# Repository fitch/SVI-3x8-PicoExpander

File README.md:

# SVI-3x8 PicoExpander

## Overview

The SVI-3x8 PicoExpander is a Raspberry Pico 2 W based expansion device for Spectravideo 318 and 328 computers.

The device emulates (when plugged into the SVI-3x8 expansion port):
 - **96 kB of additional RAM (BK22, BK31, BK32) to SVI-328**, to be used for example with BASIC SWITCH command or CP/M
 - **144 kB more RAM to SVI-318**, converting it to a SVI-328 and allowing games designed for SVI-328 to be run on a 318
 - **Disk emulation (.dsk)** so you can load and save disk images via Wi-Fi
 - **Cassette drive emulation (.cas)** with auto-running, allowing you to finally send and run .CAS images via Wi-Fi
 - **Support for 64 kB ROM game cartridges**, without using the game cartridge slot and finally fixing the 64 kB ROM support in SVI-328 MKII devices
 - **Save states** to save computer state and load it at later time, making it possible to save your progress in a game and continue later
 - **Remote launch** allowing you to pick up a game image from PC/Mac and launch it from the SVI via Wi-Fi
 - **Hard disk emulation** with server-based network backing, allowing CP/M hard disk images to be served over Wi-Fi

## Limitations

Limitations of the current software (1.4.4):
 - Supports only one disk drive, two-disk drive support coming up

## The project

This repository will later include the full software and the hardware design later as open source. Now you can access the 1.4 PCB version in [pcb](pcb/) directory.

If you can't build one yourself, you can order an assembled version from [here](https://svi-328-dev.company.site/products/svi-3x8-picoexpander-1-4). Current shipping estimate in 1-4 weeks depending on the order volumes.

<b>Important note:</b>

This is ”bleeding edge” hardware, so it might not last 40 years as the SVI did. The Pico pins are used with level shifters and within the limits of the voltage thresholds, but the actual Pico CPU is running overclocked at 300 MHz (normally 150 MHz). This might cause the Pico to wear out sooner than Raspberry has designed it to. However, the Pico can be replaced on the board if needed.

Also, note that device is a prototype and therefore has very limited warranty: you can test it when it arrives and if you're not satisfied, we'll figure out if we ship a new one or you get your money back or something else. But everything else is at your own risk. If the device stops working after 3-12 months, you'll need to fix it yourself or get a new one.

## Quick Start

### 1. Flash the Firmware

When you've built the PCB you can flash the .UF2 file provided in the [release](release/) directory. For the assembled devices, the Pico has already been flashed with the latest firmware.

1. Disconnect PicoExpander from SVI
2. Hold the **BOOTSEL** button on the Pico W while connecting it to your computer via USB
3. The Pico will appear as a USB mass storage device
4. Copy the `.uf2` firmware file from the `release/` directory to the Pico USB drive. Wait until Pico disconnects (displays Disk Not Ejected Properly in macOS) and the green LED light turns on to signal that the firmware booted correctly.
5. Finally, remove the USB cable.

### 2. Install Node.js

The file server requires Node.js to run. This project includes an `.nvmrc` file specifying Node.js v22.20.0.

**macOS (using nvm):**

Install [nvm](https://github.com/nvm-sh/nvm) if you don't have it, then:
```bash
# Install and use the correct Node.js version
nvm install
nvm use
```

**Windows:**
Download and install from [nodejs.org](https://nodejs.org/)

### 3. Boot the SVI with PicoExpander

Place the PicoExpander into the expansion port of the SVI-318 or SVI-328. Boot SVI up.

You can return to the main menu in two ways:
- Press the **RESET button** on the PicoExpander briefly
- Press **CTRL + SHIFT + LEFT GRAPH + RIGHT GRAPH** simultaneously on the keyboard

If you need to reset the SVI, press the RESET button for at least 3 seconds.

### 4. Run the File Server

Start the server with a directory containing your disk images, ROMs, and cassette files:

```bash
node js/server.js ./images
```

The server will:
- Scan the directory for supported files (.rom, .dsk, .cas, .sta)
- Connect to the PicoExpander over Wi-Fi
- Serve files to the SVI-328 on demand

Press **H** in the server to see available commands.

## Documentation

For detailed documentation, see the `doc/` directory:

| Document | Description |
|----------|-------------|
| [server.md](doc/server.md) | File server usage and interactive commands |
| [send_command.md](doc/send_command.md) | Command-line tool for scripting and automation |
| [hard-disk-emulation.md](doc/hard-disk-emulation.md) | Hard disk emulation setup and usage |
| [boot-sequence.md](doc/boot-sequence.md) | Technical details of the PicoExpander boot process |
| [io-ports.md](doc/io-ports.md) | I/O port reference for developers |
| [save-state-format.md](doc/save-state-format.md) | Save state file format specification |
| [development.md](doc/development.md) | Building the ROM and development setup |
| [pcb/README.md](pcb/README.md) | PCB design files, schematics overview, and parts list |

## Release Notes

See the latest changes in [v1.4.4 release notes](release/release-notes-1.4.4.md).

## License

Detailed licensing information is documented within the included [LICENSE](LICENSE) file.

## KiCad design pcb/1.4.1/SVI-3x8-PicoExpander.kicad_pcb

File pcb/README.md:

# SVI-3x8 PicoExpander PCB

## Overview

This directory contains the KiCad hardware design files for the SVI-3x8 PicoExpander and the SuperExpander adapter board.

## Projects

### PicoExpander (main board)

The main expansion board that connects to the SVI-3x8 expansion port via a 50-pin edge connector.

- **KiCad project:** [SVI-3x8-PicoExpander.kicad_pro](SVI-3x8-PicoExpander.kicad_pro)
- **Schematic:** [SVI-3x8-PicoExpander.kicad_sch](SVI-3x8-PicoExpander.kicad_sch)
- **PCB layout:** [SVI-3x8-PicoExpander.kicad_pcb](SVI-3x8-PicoExpander.kicad_pcb)
- **Schematics PDF:** [schematics.pdf](../photos/schematics.pdf)

### SuperExpander Adapter

A simple passive adapter board that allows the PicoExpander to be connected to the Spectravideo SuperExpander (SVI-605) instead of directly to the computer's expansion port.

- **KiCad project:** [SVI-3x8-PicoExpander-SuperExpander-adapter.kicad_pro](SVI-3x8-PicoExpander-SuperExpander-adapter.kicad_pro)
- **PCB layout:** [SVI-3x8-PicoExpander-SuperExpander-adapter.kicad_pcb](SVI-3x8-PicoExpander-SuperExpander-adapter.kicad_pcb)

### Gerber Files

Manufacturing-ready Gerber files are available in the [gerber/](gerber/) directory:

- [gerber/PicoExpander/](gerber/PicoExpander/) — Main board Gerbers
- [gerber/SuperExpander adapter/](gerber/SuperExpander%20adapter/) — Adapter board Gerbers

## Schematics Overview

The PicoExpander circuit consists of:

- **Raspberry Pi Pico 2 W (A1)** — The main microcontroller running the emulation firmware at 300 MHz. Connects to the SVI bus through level shifters and handles all emulation logic, Wi-Fi connectivity, and flash storage.

- **4x 74LVC245A level shifters (U1, U2, U4, U5)** — Bidirectional bus transceivers that translate between the SVI's 5V bus and the Pico's 3.3V logic levels:
  - **U5** — Data bus write (SVI → Pico, active during bus writes)
  - **U1** — Data bus read (Pico → SVI, active during bus reads)
  - **U2** — Lower address bus A0–A7
  - **U4** — Higher address bus A8–A15

- **74HC14 Schmitt trigger (U3, 7 gates used)** — Provides clean signal conditioning for active-low control signals from the SVI bus: `/RST`, `/ROMDIS`, `/RD`, `/WR`, `/MREQ`, `/P_AE` (address enable), and `/P_RD_DE`/`/P_WR_DE` (data direction enable).

- **50-pin edge connector (J1)** — Interfaces directly with the SVI-3x8 expansion bus, providing access to the full address bus, data bus, and control signals.

- **Reset button (SW1)** — Short press returns to the PicoExpander menu. Long press (3+ seconds) resets the SVI.

- **Pull-up resistor (R1, 10kΩ)** — Pull-up on the reset line.

- **Decoupling capacitors (C2–C5, 0.1μF)** — One per level shifter IC for power supply filtering.

## Parts List

| Ref | Qty | Description | DigiKey Part | DigiKey # |
|-----|-----|-------------|-------------|-----------|
| A1 | 1 | Raspberry Pi Pico 2 W (RP2350) | [SC1634](https://www.digikey.com/en/products/detail/raspberry-pi/SC1634/26241087) | 2648-SC1634-ND |
| U1, U2, U4, U5 | 4 | 74LVC245A — Bidirectional level shifter, 3.6V, 20-PDIP | [SN74LVC245AN](https://www.digikey.com/en/products/detail/texas-instruments/SN74LVC245AN/377483) | 296-8503-5-ND |
| U3 | 1 | 74HC14 — Hex Schmitt trigger inverter, 14-DIP | [SN74AHCT14N](https://www.digikey.com/en/products/detail/texas-instruments/SN74AHCT14N/375854) | 296-4674-5-ND |
| C2–C5 | 4 | 0.1μF ceramic capacitor, 50V, X7R, radial | [K104K15X7RF5TL2](https://www.digikey.com/en/products/detail/vishay-beyschlag-draloric-bc-components/K104K15X7RF5TL2/286538) | BC1084CT-ND |
| R1 | 1 | 10kΩ resistor, 1/4W, 1%, axial | [MFR-25FRF52-10K](https://www.digikey.com/en/products/detail/yageo/MFR-25FRF52-10K/14626) | 13-MFR-25FRF52-10KCT-ND |
| J1 | 1 | 50-pin (2x25) card edge connector, dual female, 0.100" pitch | [395-050-524-202](https://www.digikey.com/en/products/detail/edac-inc/395-050-524-202/1297302) | 395-050-524-202-ND |
| SW1 | 1 | Tactile push button switch, SPST-NO, 0.05A, 12V | [PTS636 SP43 LFS](https://www.digikey.com/product-detail/en/c-k/PTS636-SP43-LFS/CKN12304-ND/10071717) | CKN12304-ND |

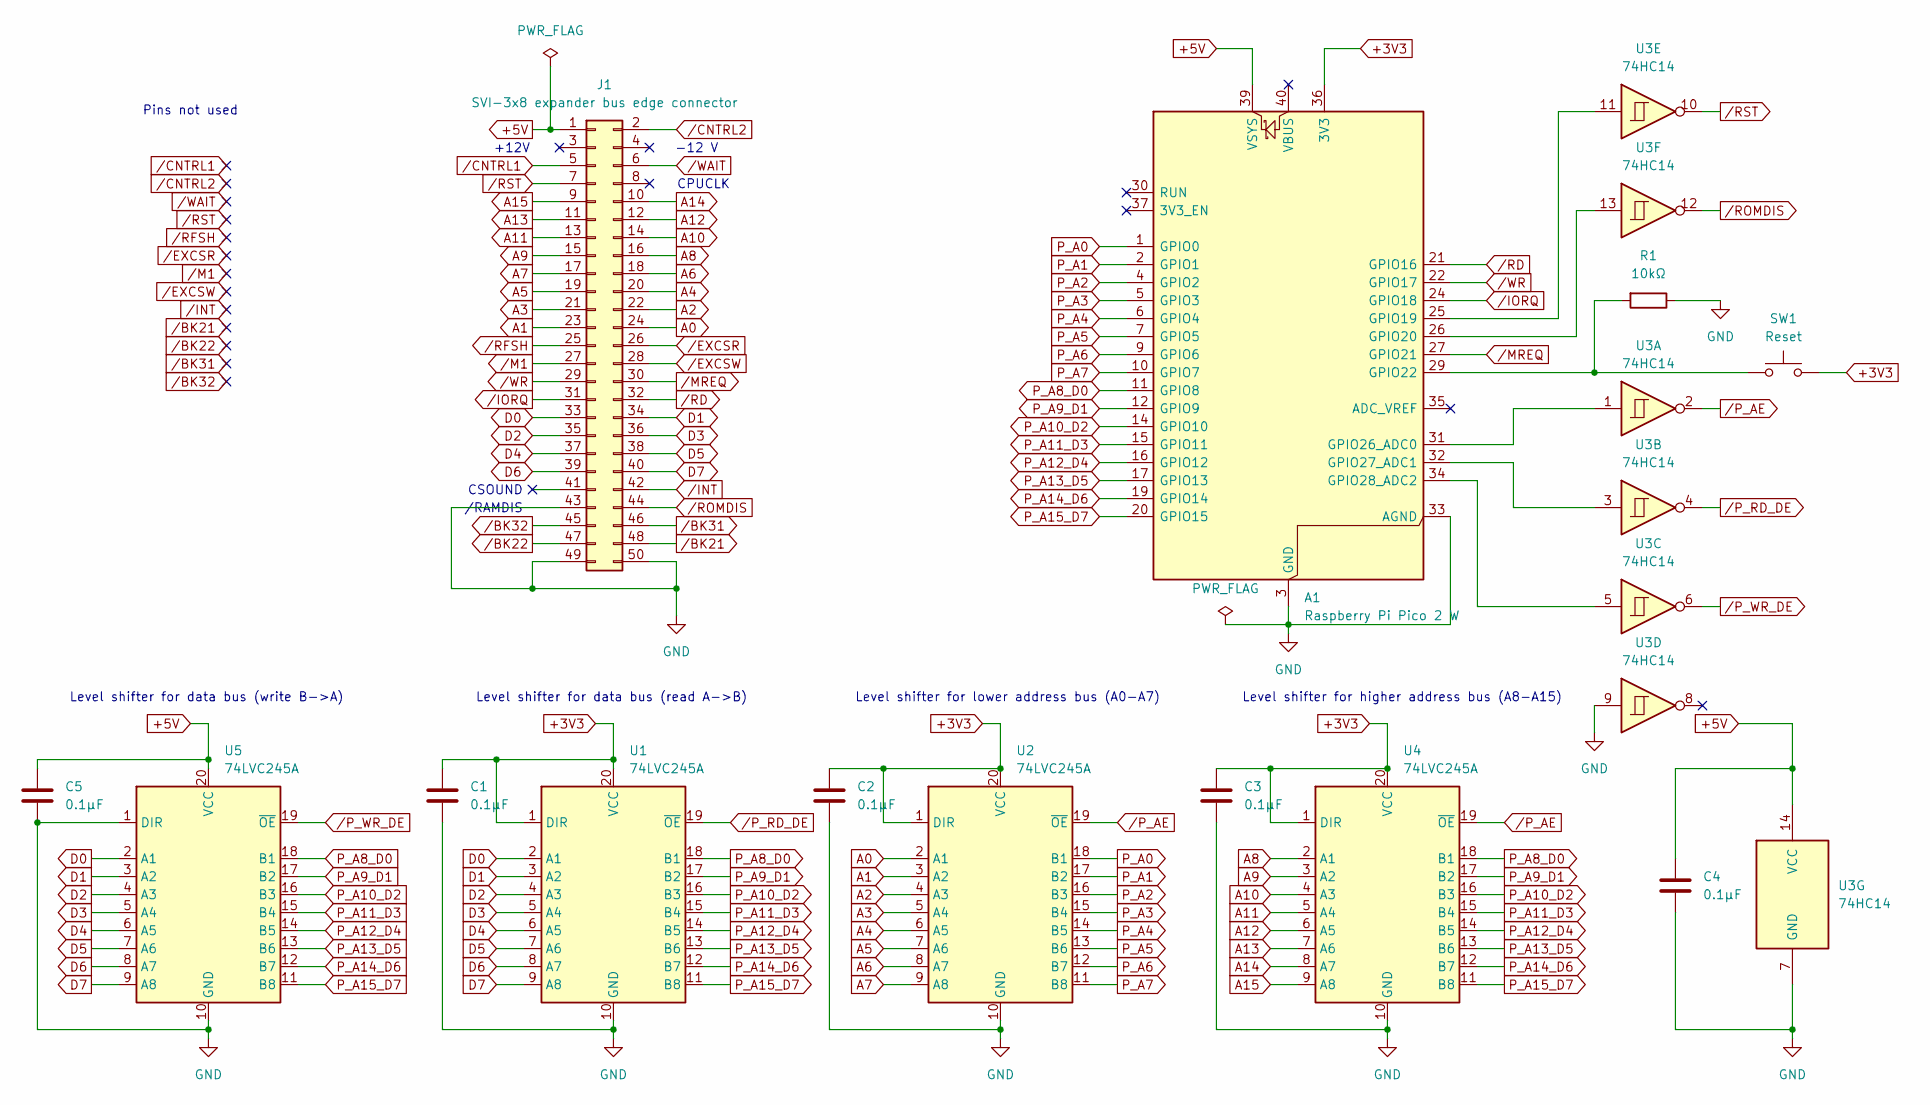
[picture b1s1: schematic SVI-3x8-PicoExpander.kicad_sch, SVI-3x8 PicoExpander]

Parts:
A1: Raspberry Pi Pico 2 W; RaspberryPi_Pico_Common_Unspecified
C1, C2, C3, C4, C5: 0.1μF; C_Disc_D3.0mm_W1.6mm_P2.50mm
J1: SVI-3x8 expander bus edge connector; DIP-50_EXPANDER_BUS
R1: 10kΩ; R_Axial_DIN0207_L6.3mm_D2.5mm_P7.62mm_Horizontal
SW1: Reset; SW_PUSH_1P1T_6x3.5mm_H4.3_APEM_MJTP1243
U1, U2, U4, U5: 74LVC245A; DIP-20_W7.62mm
U3: 74HC14; DIP-14_W7.62mm

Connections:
+3V3: A1.36 (3V3), C1.1, C2.1, C3.1, SW1.2, U1.1 (DIR), U1.20 (VCC), U2.1 (DIR), U2.20 (VCC), U4.1 (DIR), U4.20 (VCC)
+5V: A1.39 (VSYS), C4.1, C5.1, J1.1, U3.14 (VCC), U5.20 (VCC)
A0: J1.24, U2.2 (A1)
A1: J1.23, U2.3 (A2)
A2: J1.22, U2.4 (A3)
A3: J1.21, U2.5 (A4)
A4: J1.20, U2.6 (A5)
A5: J1.19, U2.7 (A6)
A6: J1.18, U2.8 (A7)
A7: J1.17, U2.9 (A8)
A8: J1.16, U4.2 (A1)
A9: J1.15, U4.3 (A2)
A10: J1.14, U4.4 (A3)
A11: J1.13, U4.5 (A4)
A12: J1.12, U4.6 (A5)
A13: J1.11, U4.7 (A6)
A14: J1.10, U4.8 (A7)
A15: J1.9, U4.9 (A8)
D0: J1.33, U1.2 (A1), U5.2 (A1)
D1: J1.34, U1.3 (A2), U5.3 (A2)
D2: J1.35, U1.4 (A3), U5.4 (A3)
D3: J1.36, U1.5 (A4), U5.5 (A4)
D4: J1.37, U1.6 (A5), U5.6 (A5)
D5: J1.38, U1.7 (A6), U5.7 (A6)
D6: J1.39, U1.8 (A7), U5.8 (A7)
D7: J1.40, U1.9 (A8), U5.9 (A8)
GND: A1.3 (GND), A1.8 (GND), A1.13 (GND), A1.18 (GND), A1.23 (GND), A1.28 (GND), A1.33 (AGND), A1.38 (GND), C1.2, C2.2, C3.2, C4.2, C5.2, J1.43, J1.49, J1.50, R1.1, U1.10 (GND), U2.10 (GND), U3.7 (GND), U3.9, U4.10 (GND), U5.1 (DIR), U5.10 (GND)
unnamed: A1.25 (GPIO19), U3.11
unnamed: A1.26 (GPIO20), U3.13
unnamed: A1.29 (GPIO22), R1.2, SW1.1
unnamed: A1.31 (GPIO26_ADC0), U3.1
unnamed: A1.32 (GPIO27_ADC1), U3.3
unnamed: A1.34 (GPIO28_ADC2), U3.5
P_A0: A1.1 (GPIO0), U2.18 (B1)
P_A1: A1.2 (GPIO1), U2.17 (B2)
P_A2: A1.4 (GPIO2), U2.16 (B3)
P_A3: A1.5 (GPIO3), U2.15 (B4)
P_A4: A1.6 (GPIO4), U2.14 (B5)
P_A5: A1.7 (GPIO5), U2.13 (B6)
P_A6: A1.9 (GPIO6), U2.12 (B7)
P_A7: A1.10 (GPIO7), U2.11 (B8)
P_A8_D0: A1.11 (GPIO8), U1.18 (B1), U4.18 (B1), U5.18 (B1)
P_A9_D1: A1.12 (GPIO9), U1.17 (B2), U4.17 (B2), U5.17 (B2)
P_A10_D2: A1.14 (GPIO10), U1.16 (B3), U4.16 (B3), U5.16 (B3)
P_A11_D3: A1.15 (GPIO11), U1.15 (B4), U4.15 (B4), U5.15 (B4)
P_A12_D4: A1.16 (GPIO12), U1.14 (B5), U4.14 (B5), U5.14 (B5)
P_A13_D5: A1.17 (GPIO13), U1.13 (B6), U4.13 (B6), U5.13 (B6)
P_A14_D6: A1.19 (GPIO14), U1.12 (B7), U4.12 (B7), U5.12 (B7)
P_A15_D7: A1.20 (GPIO15), U1.11 (B8), U4.11 (B8), U5.11 (B8)
/BK21: J1.48
/BK22: J1.47
/BK31: J1.46
/BK32: J1.45
/CNTRL1: J1.5
/CNTRL2: J1.2
/EXCSR: J1.26
/EXCSW: J1.28
/INT: J1.42
/IORQ: A1.24 (GPIO18), J1.31
/M1: J1.27
/MREQ: A1.27 (GPIO21), J1.30
/P_AE: U2.19 (~OE), U3.2, U4.19 (~OE)
/P_RD_DE: U1.19 (~OE), U3.4
/P_WR_DE: U3.6, U5.19 (~OE)
/RD: A1.21 (GPIO16), J1.32
/RFSH: J1.25
/ROMDIS: J1.44, U3.12
/RST: J1.7, U3.10
/WAIT: J1.6
/WR: A1.22 (GPIO17), J1.29

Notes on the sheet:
-12 V
+12V
Level shifter for data bus (read A->B)
CSOUND
Level shifter for data bus (write B->A)
Level shifter for higher address bus (A8-A15)
Level shifter for lower address bus (A0-A7)
CPUCLK
/RAMDIS
Pins not used

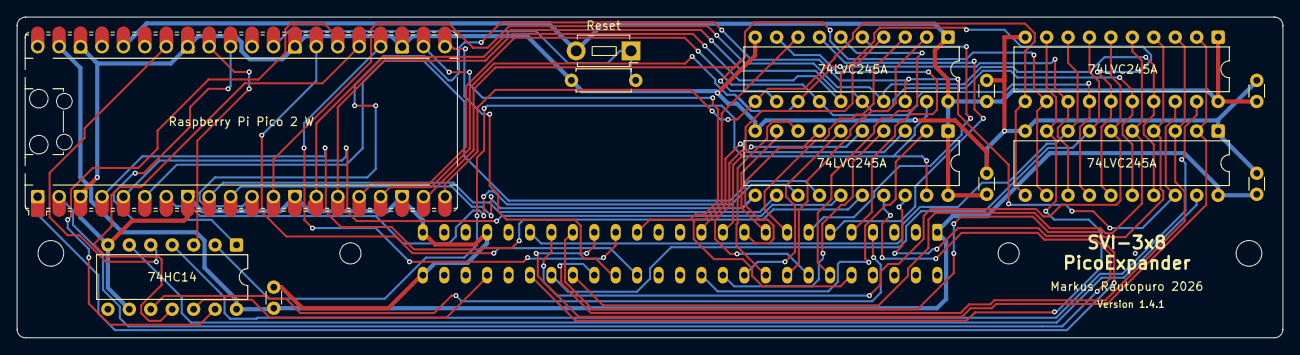
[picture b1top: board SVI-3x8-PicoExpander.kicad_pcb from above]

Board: 2 copper layers, 150.0 x 38.0 mm, 14 parts (1 on the bottom side), 58 nets.

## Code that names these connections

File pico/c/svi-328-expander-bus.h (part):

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 */

/*
    A0..A15 -> GPIO0..15
    D0..D7 <-> GPIO8..15

    /RD -> GPIO16
    /WR -> GPIO17
    /IORQ -> GPIO18
    /MREQ -> GPIO21

    RST -> GPIO19 (inverted /RST)
    ROMDIS <- GPIO20 (inverted /ROMDIS)
    Reset button -> GPIO22

    P_AE <- GPIO23 (Enable address line read)
    P_RD_DE <- GPIO24 (Enable data line read)
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
#define OTHER_PIN_MASK (P_AE_GPIO_MASK | P_RD_DE_GPIO_MASK | P_WR_DE_GPIO_MASK | RD_GPIO_MASK | WR_GPIO_MASK | IORQ_GPIO_MASK | MREQ_GPIO_MASK | RST_GPIO_MASK | RESET_BUTTON_GPIO_MASK | ROMDIS_GPIO_MASK)
#define ADDRESS_PIN_MASK ((1UL << 16) - 1)
#define DATA_PIN_MASK (((1UL << 8) - 1) << 8) // Data pins shared with higher address pins in GPIO8..15
#define ALL_GPIO_MASK (ADDRESS_PIN_MASK | OTHER_PIN_MASK)
#define IORQ_PORT_PIN_MASK ((1UL << 8) - 1) // I/O port pins are GPIO0..7

#define SSID_MAX_LENGTH 32
#define PASSWORD_MAX_LENGTH 63
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
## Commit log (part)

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2025-09-02 Initial version
2025-09-02 Add initial README.md
2025-09-28 Add --ignore-size flag
2026-01-04 Add photos
2026-01-04 Add LICENSE
2026-04-05 Fix the following bugs: .CAS autoload causing Syntax error, Dump disk appearing erroneously on the menu after warm reset, catalog filter not resetting properly after warm reset and some text overflow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

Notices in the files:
pico/c/svi-328-expander-bus.h:
Copyright (c) 2026 Markus Rautopuro
